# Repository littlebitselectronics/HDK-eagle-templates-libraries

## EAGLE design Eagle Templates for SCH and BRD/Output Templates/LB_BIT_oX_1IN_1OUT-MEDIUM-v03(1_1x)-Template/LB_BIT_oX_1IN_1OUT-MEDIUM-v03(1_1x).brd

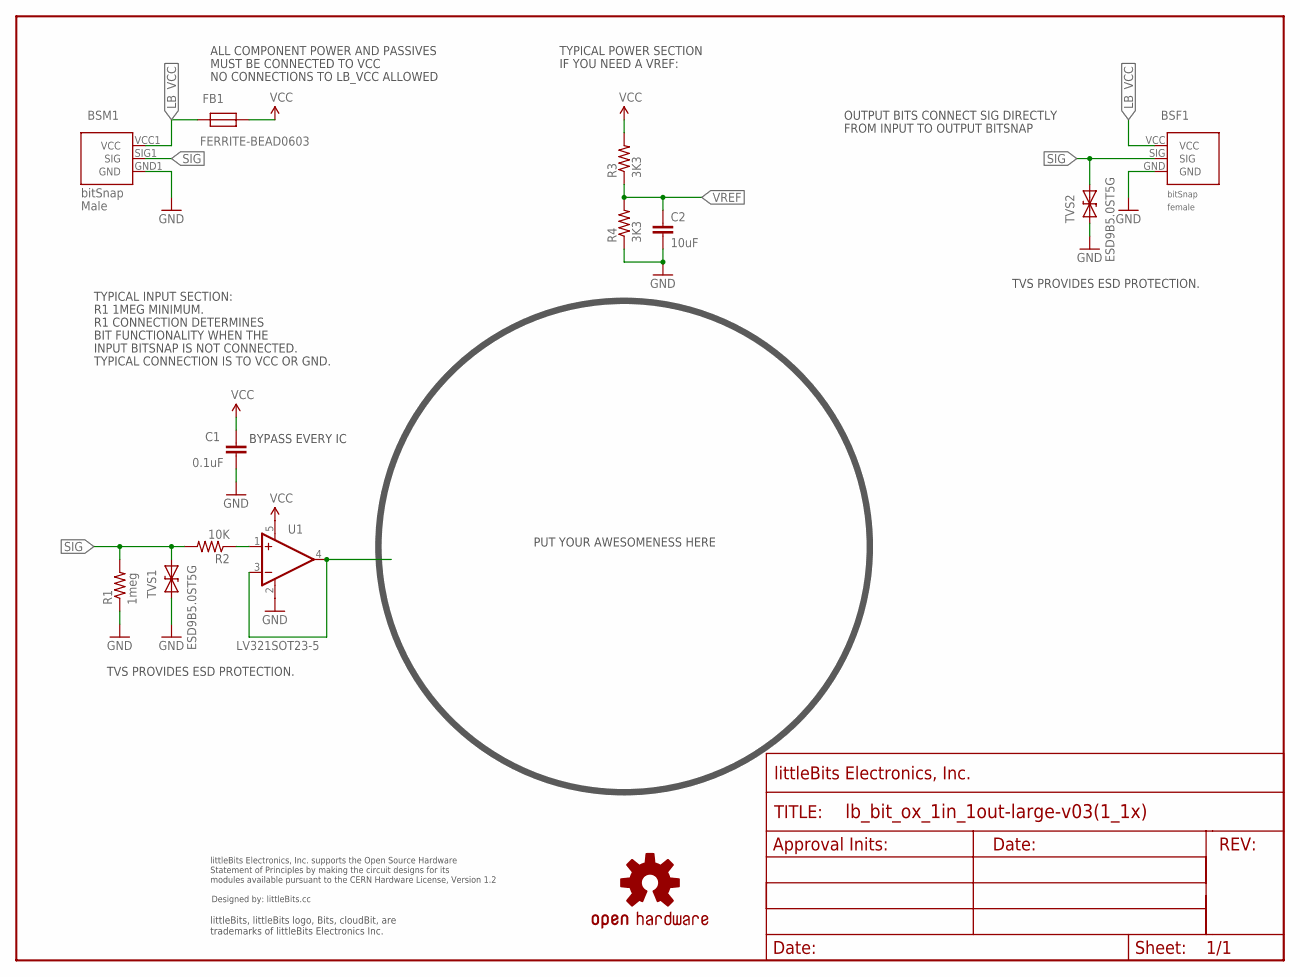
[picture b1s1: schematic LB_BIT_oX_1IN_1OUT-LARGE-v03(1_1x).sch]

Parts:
BSF1: BITSNAP_V03_FEMALE
BSM1: BITSNAP_V03_MALE
C1: 0.1uF; CAP-0603
C2: 10uF; CAP-0603
FB1: FERRITE-BEAD0603; R0603
R1: 1meg; RES-0603
R2: 10K; RES-0603
R3, R4: 3K3; RES-0603
TVS1, TVS2: ESD9B5.0ST5G; SOD-923
U1: LV321SOT23-5; SOT23-5
U$1: OSHW-LOGOL; OSHW-LOGO-L
U$2: OSHWCREDIT
U$3: FRAME-LETTER; FABDWG01-OHW

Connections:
GND: BSF1.GND, BSM1.GND1 (GND), C1.2, C2.2, R1.1, R4.1, TVS1.1 (A), TVS2.1 (A), U1.2 (V-)
LB_VCC: BSF1.VCC, BSM1.VCC1 (VCC), FB1.2
unnamed: U1.3 (-IN), U1.4 (OUT)
unnamed: R2.1, U1.1 (+IN)
SIG: BSF1.SIG, BSM1.SIG1 (SIG), R1.2, R2.2, TVS1.2 (C), TVS2.2 (C)
VCC: C1.1, FB1.1, R3.2, U1.5 (V+)
VREF: C2.1, R3.1, R4.2

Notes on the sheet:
R1 1MEG MINIMUM.
R1 CONNECTION DETERMINES
BIT FUNCTIONALITY WHEN THE
INPUT BITSNAP IS NOT CONNECTED.
TYPICAL CONNECTION IS TO VCC OR GND.
TVS PROVIDES ESD PROTECTION.
TYPICAL INPUT SECTION:
TYPICAL POWER SECTION
IF YOU NEED A VREF:
PUT YOUR AWESOMENESS HERE
BYPASS EVERY IC
NO CONNECTIONS TO LB_VCC ALLOWED
ALL COMPONENT POWER AND PASSIVES
MUST BE CONNECTED TO VCC
OUTPUT BITS CONNECT SIG DIRECTLY
FROM INPUT TO OUTPUT BITSNAP

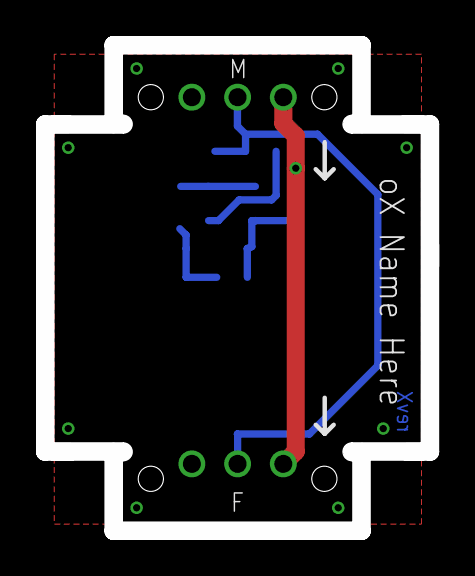
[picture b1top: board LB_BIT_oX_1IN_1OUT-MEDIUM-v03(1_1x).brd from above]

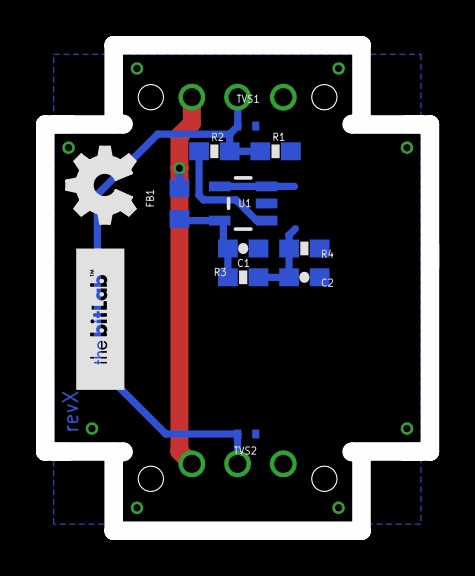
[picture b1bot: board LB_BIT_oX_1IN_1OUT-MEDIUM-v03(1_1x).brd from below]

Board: 2 copper layers, 20.4 x 26.0 mm, 17 parts (11 on the bottom side), 7 nets.

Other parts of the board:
U$4: OSHW_FILLX150_NOTEXT
U$5: BITLAB-LOGO

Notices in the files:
parts and their libraries:
LITTLEBITS: modules available pursuant to the CERN Hardware License,
Version 1.2
LITTLEBITS: modules available pursuant to the CERN Hardware License, Version 1.2
